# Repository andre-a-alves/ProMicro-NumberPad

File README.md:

# ProMicro-NumberPad

This is a simple learning project that includes the design for a simple numpad PCB that is designed to work with an Arduino-compatible Sparkfun Pro Micro.
The PCB is designed in Autodesk Eagle, and the C code is written for the Arduino IDE.

## PCB

## License
This project is licensed under the [GNU General Purpose License v3.0](LICENSE).

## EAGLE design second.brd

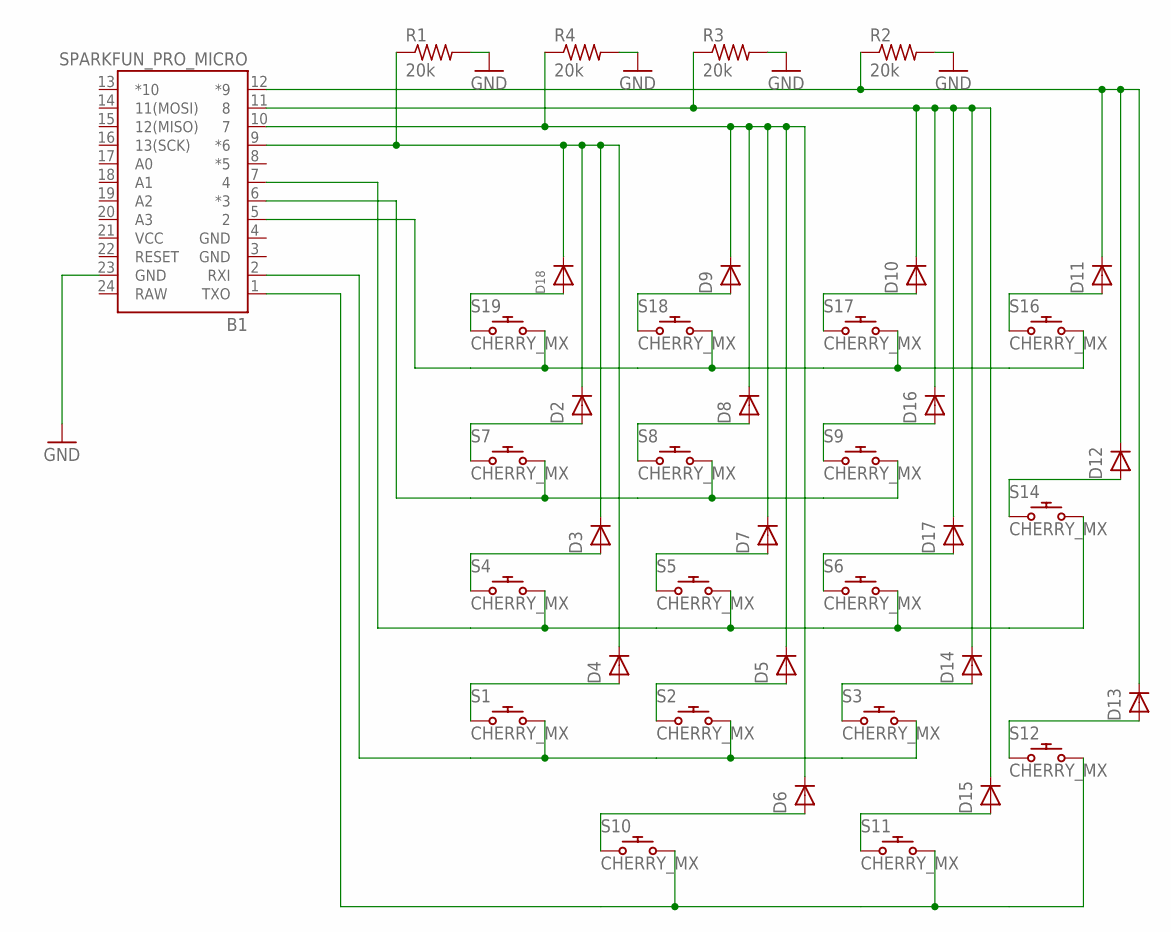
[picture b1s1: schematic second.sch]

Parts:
B1: SPARKFUN_PRO_MICRO
D2, D3, D4, D5, D6, D7, D8, D9, D10, D11, D12, D13, D14, D15, D16, D17, D18: DIODESOD-123; SOD-123
R1, R2, R3, R4: 20k; R0805
S1, S2, S3, S4, S5, S6, S7, S8, S9, S10, S11, S12, S14, S16, S17, S18, S19: CHERRY_MX

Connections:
GND: B1.3 (GND), B1.4 (GND), B1.23 (GND), R1.2, R2.2, R3.2, R4.2
unnamed: D3.A, S4.S1 (1)
unnamed: D2.A, S7.S1 (1)
unnamed: D6.A, S10.S1 (1)
unnamed: D4.A, S1.S1 (1)
unnamed: D7.A, S5.S1 (1)
unnamed: D8.A, S8.S1 (1)
unnamed: D15.A, S11.S1 (1)
unnamed: D16.A, S9.S1 (1)
unnamed: D17.A, S6.S1 (1)
unnamed: D5.A, S2.S1 (1)
unnamed: D14.A, S3.S1 (1)
unnamed: D13.A, S12.S1 (1)
unnamed: D10.A, S17.S1 (1)
unnamed: D12.A, S14.S1 (1)
unnamed: D9.A, S18.S1 (1)
unnamed: B1.9 (*6), D2.C, D3.C, D4.C, D18.C, R1.1
unnamed: D18.A, S19.S1 (1)
unnamed: D11.A, S16.S1 (1)
unnamed: B1.1 (TXO), S10.S2 (2), S11.S2 (2), S12.S2 (2)
unnamed: B1.2 (RXI), S1.S2 (2), S2.S2 (2), S3.S2 (2)
unnamed: B1.7 (4), S4.S2 (2), S5.S2 (2), S6.S2 (2), S14.S2 (2)
unnamed: B1.6 (*3), S7.S2 (2), S8.S2 (2), S9.S2 (2)
unnamed: B1.5 (2), S16.S2 (2), S17.S2 (2), S18.S2 (2), S19.S2 (2)
unnamed: B1.10 (7), D5.C, D6.C, D7.C, D8.C, D9.C, R4.1
unnamed: B1.11 (8), D10.C, D14.C, D15.C, D16.C, D17.C, R3.1
unnamed: B1.12 (*9), D11.C, D12.C, D13.C, R2.1
RAW: B1.24 (RAW)
VCC: B1.21 (VCC)

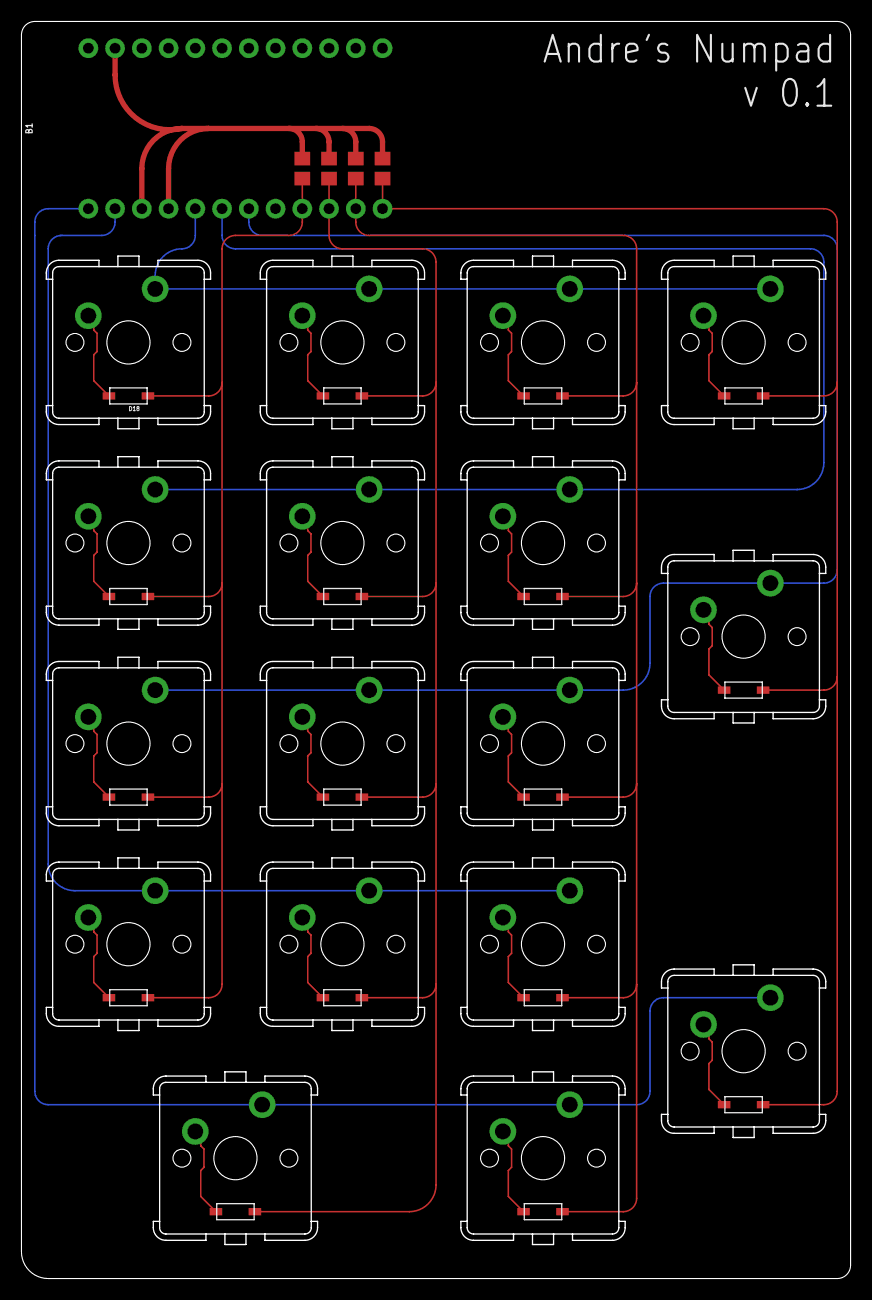
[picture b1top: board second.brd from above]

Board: 2 copper layers, 78.7 x 119.3 mm, 39 parts (0 on the bottom side), 27 nets.

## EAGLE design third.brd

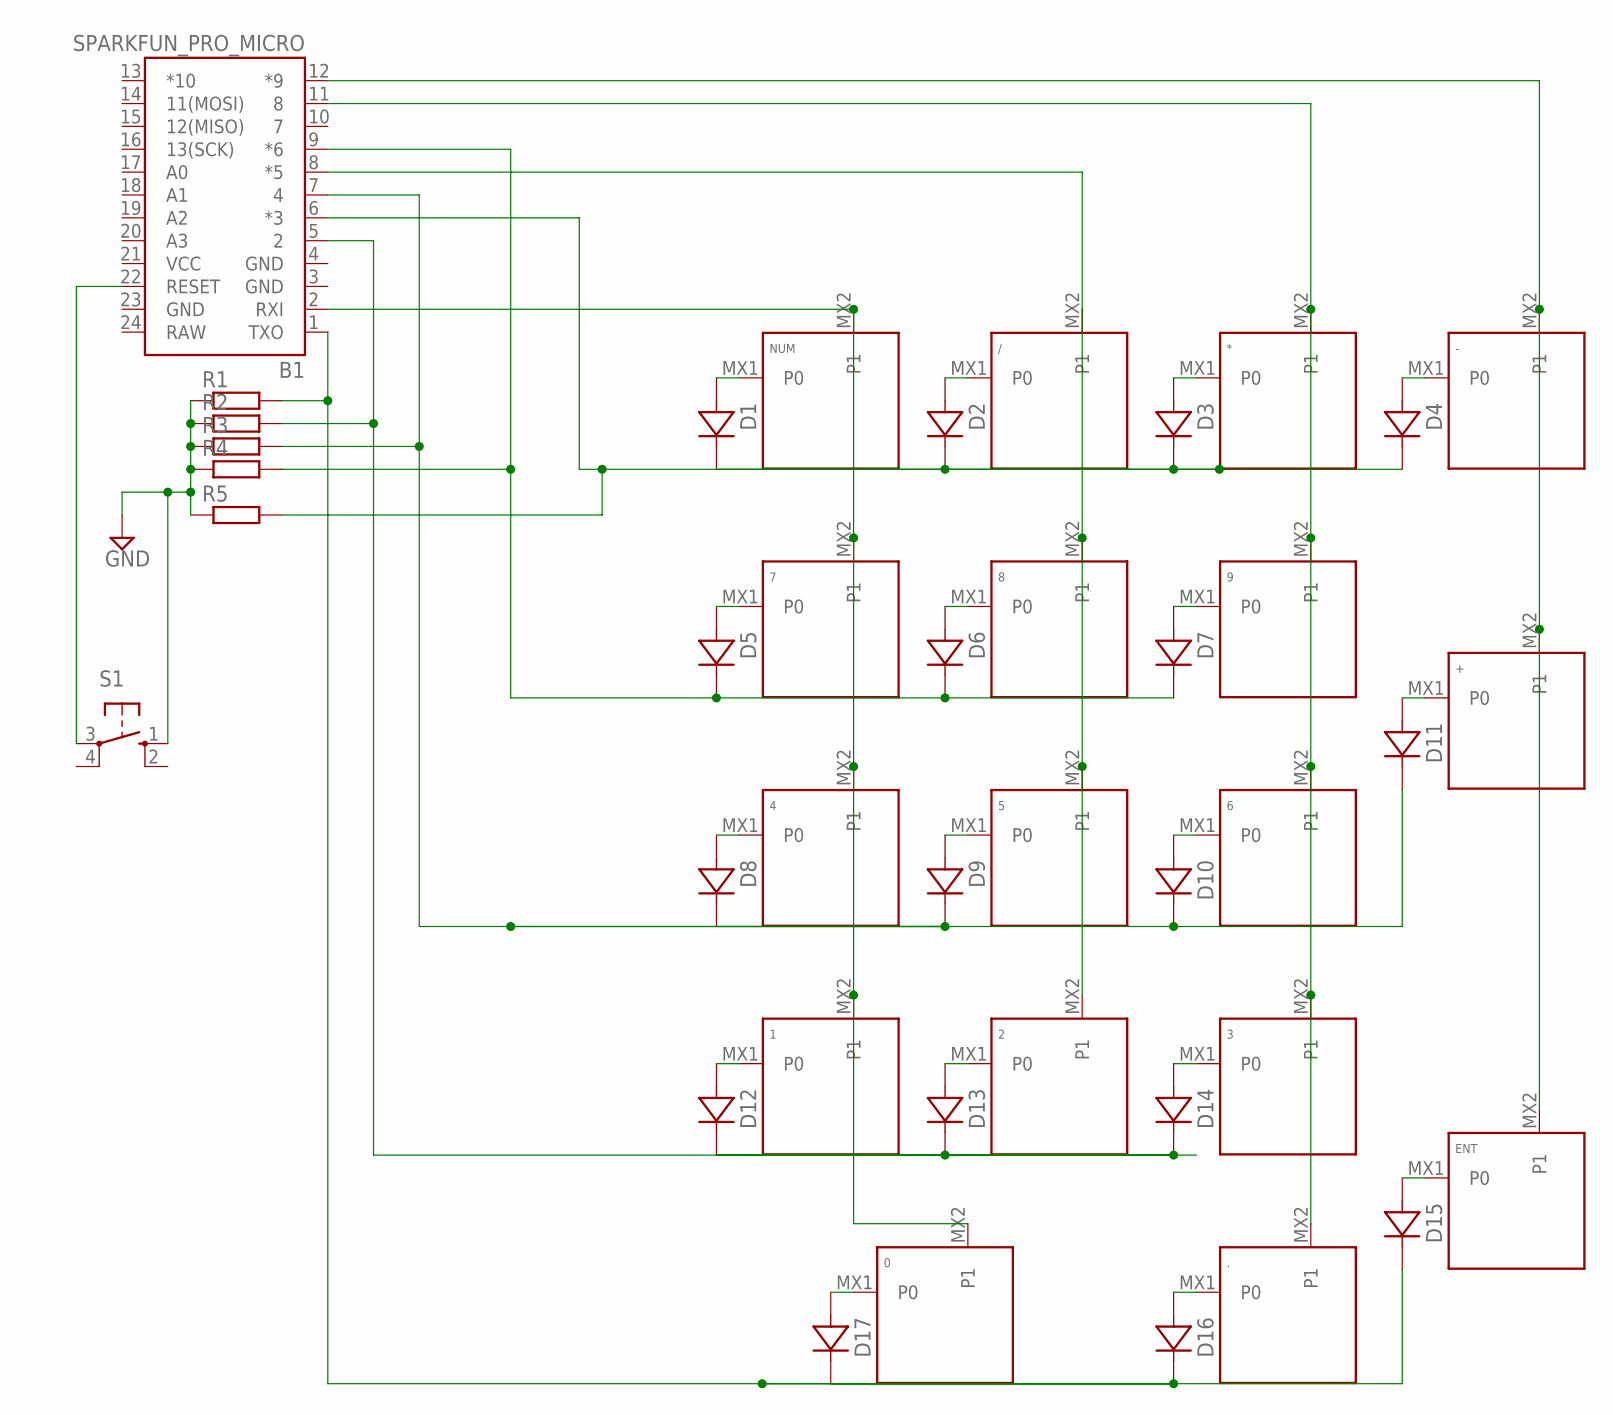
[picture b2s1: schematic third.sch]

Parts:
0: KEYSWITCH-PLAIN-MX-2U-FLIPPED; MX-2U-FLIPPED
1, 2, 3, 4, 5, 6, 7, 8, 9, .: KEYSWITCH-PLAIN-MX-1U; MX-1U
*: KEYSWITCH-PLAIN-MX-1U; MX-1U
+: KEYSWITCH-PLAIN-MX-2U-ROTATED; MX-2U-ROTATED
-: KEYSWITCH-PLAIN-MX-1U; MX-1U
/: KEYSWITCH-PLAIN-MX-1U; MX-1U
B1: SPARKFUN_PRO_MICRO
D1, D2, D3, D4, D5, D6, D7, D8, D9, D10, D11, D12, D13, D14, D15, D16, D17: 1N4148; DIODE_HAND
ENT: KEYSWITCH-PLAIN-MX-2U-ROTATED; MX-2U-ROTATED
NUM: KEYSWITCH-PLAIN-MX-1U; MX-1U
R1, R2, R3, R4, R5: RESISTOR-THT; THT-RESISTOR
S1: 10-XX; B3F-10XX

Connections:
GND: B1.3 (GND), B1.4 (GND), B1.23 (GND), R1.1, R2.1, R3.1, R4.1, R5.1, S1.1 (S)
unnamed: D1.A1 (A), D1.A2 (A), D1.A3 (A), NUM.MX1 (P0)
unnamed: /.MX1 (P0), D2.A1 (A), D2.A2 (A), D2.A3 (A)
unnamed: *.MX1 (P0), D3.A1 (A), D3.A2 (A), D3.A3 (A)
unnamed: -.MX1 (P0), D4.A1 (A), D4.A2 (A), D4.A3 (A)
unnamed: 7.MX1 (P0), D5.A1 (A), D5.A2 (A), D5.A3 (A)
unnamed: 8.MX1 (P0), D6.A1 (A), D6.A2 (A), D6.A3 (A)
unnamed: 9.MX1 (P0), D7.A1 (A), D7.A2 (A), D7.A3 (A)
unnamed: 4.MX1 (P0), D8.A1 (A), D8.A2 (A), D8.A3 (A)
unnamed: 5.MX1 (P0), D9.A1 (A), D9.A2 (A), D9.A3 (A)
unnamed: 6.MX1 (P0), D10.A1 (A), D10.A2 (A), D10.A3 (A)
unnamed: +.MX1 (P0), D11.A1 (A), D11.A2 (A), D11.A3 (A)
unnamed: 1.MX1 (P0), D12.A1 (A), D12.A2 (A), D12.A3 (A)
unnamed: 2.MX1 (P0), D13.A1 (A), D13.A2 (A), D13.A3 (A)
unnamed: 3.MX1 (P0), D14.A1 (A), D14.A2 (A), D14.A3 (A)
unnamed: D15.A1 (A), D15.A2 (A), D15.A3 (A), ENT.MX1 (P0)
unnamed: ..MX1 (P0), D16.A1 (A), D16.A2 (A), D16.A3 (A)
unnamed: 0.MX1 (P0), D17.A1 (A), D17.A2 (A), D17.A3 (A)
unnamed: 0.MX2 (P1), 1.MX2 (P1), 4.MX2 (P1), 7.MX2 (P1), B1.2 (RXI), NUM.MX2 (P1)
unnamed: 2.MX2 (P1), 5.MX2 (P1), 8.MX2 (P1), /.MX2 (P1), B1.8 (*5)
unnamed: 3.MX2 (P1), 6.MX2 (P1), 9.MX2 (P1), *.MX2 (P1), ..MX2 (P1), B1.11 (8)
unnamed: B1.6 (*3), D1.C1 (C), D1.C2 (C), D1.C3 (C), D2.C1 (C), D2.C2 (C), D2.C3 (C), D3.C1 (C), D3.C2 (C), D3.C3 (C), D4.C1 (C), D4.C2 (C), D4.C3 (C), R5.2
unnamed: B1.9 (*6), D5.C1 (C), D5.C2 (C), D5.C3 (C), D6.C1 (C), D6.C2 (C), D6.C3 (C), D7.C1 (C), D7.C2 (C), D7.C3 (C), R4.2
unnamed: B1.7 (4), D8.C1 (C), D8.C2 (C), D8.C3 (C), D9.C1 (C), D9.C2 (C), D9.C3 (C), D10.C1 (C), D10.C2 (C), D10.C3 (C), D11.C1 (C), D11.C2 (C), D11.C3 (C), R3.2
unnamed: B1.5 (2), D12.C1 (C), D12.C2 (C), D12.C3 (C), D13.C1 (C), D13.C2 (C), D13.C3 (C), D14.C1 (C), D14.C2 (C), D14.C3 (C), R2.2
unnamed: B1.1 (TXO), D15.C1 (C), D15.C2 (C), D15.C3 (C), D16.C1 (C), D16.C2 (C), D16.C3 (C), D17.C1 (C), D17.C2 (C), D17.C3 (C), R1.2
unnamed: B1.22 (RESET), S1.3
unnamed: +.MX2 (P1), -.MX2 (P1), B1.12 (*9), ENT.MX2 (P1)
RAW: B1.24 (RAW)
VCC: B1.21 (VCC)

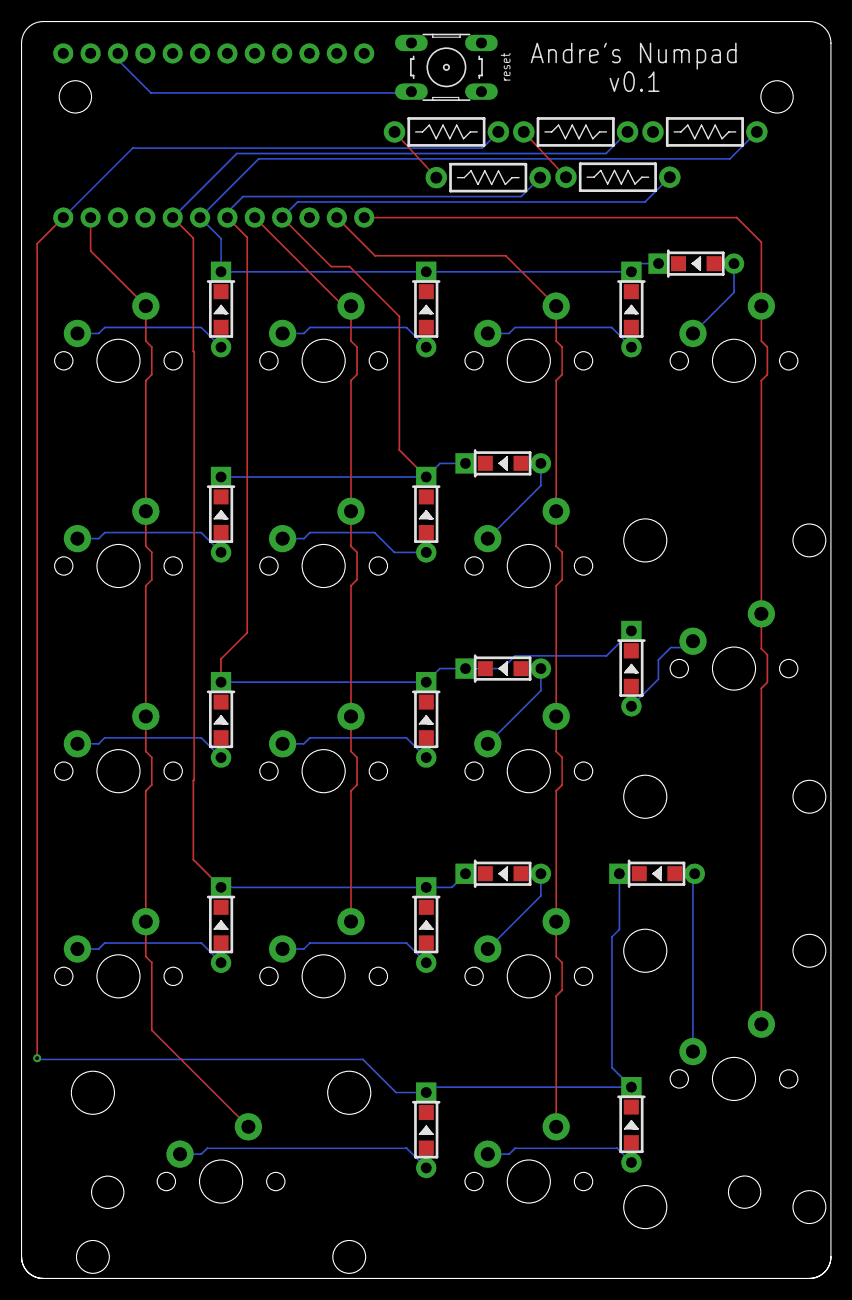
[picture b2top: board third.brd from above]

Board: 2 copper layers, 75.2 x 116.7 mm, 41 parts (0 on the bottom side), 28 nets.

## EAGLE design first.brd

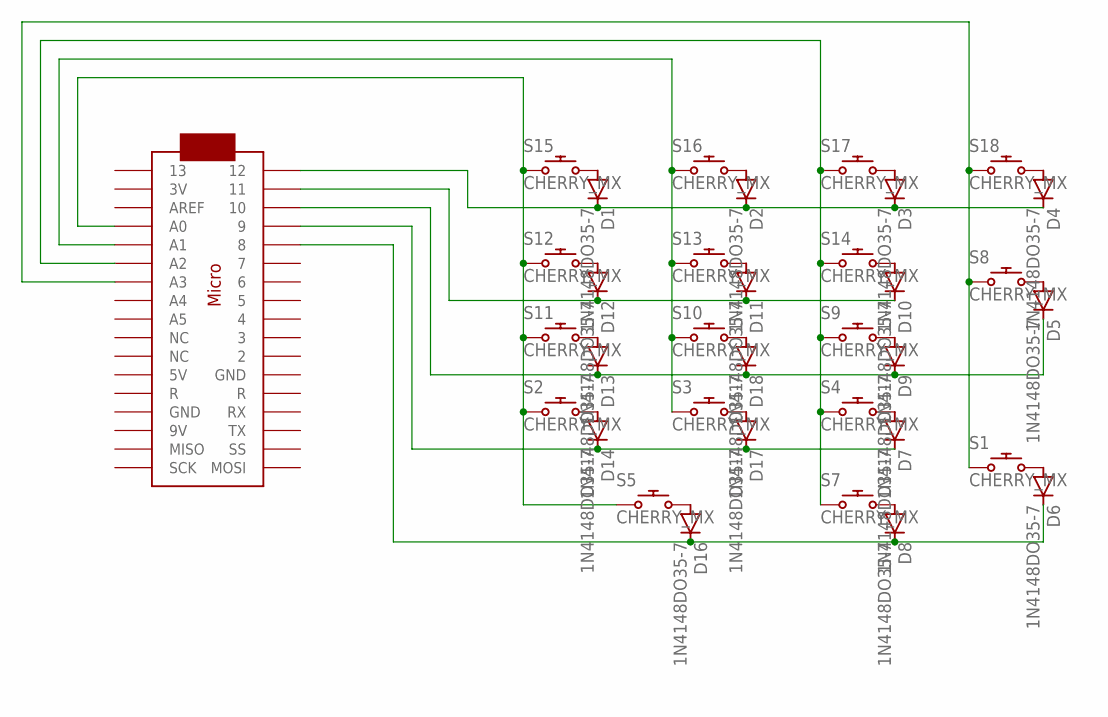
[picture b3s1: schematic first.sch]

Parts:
D1, D2, D3, D4, D5, D6, D7, D8, D9, D10, D11, D12, D13, D14, D16, D17, D18: 1N4148DO35-7; DO35-7
S1, S2, S3, S4, S5, S7, S8, S9, S10, S11, S12, S13, S14, S15, S16, S17, S18: CHERRY_MX
U$1: ARDUINOMICRO

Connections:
unnamed: S2.S1 (1), S5.S1 (1), S11.S1 (1), S12.S1 (1), S15.S1 (1), U$1.P$31 (A0)
unnamed: S3.S1 (1), S10.S1 (1), S13.S1 (1), S16.S1 (1), U$1.P$30 (A1)
unnamed: S4.S1 (1), S7.S1 (1), S9.S1 (1), S14.S1 (1), S17.S1 (1), U$1.P$29 (A2)
unnamed: S1.S1 (1), S8.S1 (1), S18.S1 (1), U$1.P$28 (A3)
unnamed: D1.C, D2.C, D3.C, D4.C, U$1.P$1 (12)
unnamed: D10.C, D11.C, D12.C, U$1.P$2 (11)
unnamed: D5.C, D9.C, D13.C, D18.C, U$1.P$3 (10)
unnamed: D7.C, D14.C, D17.C, U$1.P$4 (9)
unnamed: D6.C, D8.C, D16.C, U$1.P$5 (8)
unnamed: D1.A, S15.S2 (2)
unnamed: D2.A, S16.S2 (2)
unnamed: D3.A, S17.S2 (2)
unnamed: D4.A, S18.S2 (2)
unnamed: D5.A, S8.S2 (2)
unnamed: D6.A, S1.S2 (2)
unnamed: D7.A, S4.S2 (2)
unnamed: D8.A, S7.S2 (2)
unnamed: D9.A, S9.S2 (2)
unnamed: D10.A, S14.S2 (2)
unnamed: D11.A, S13.S2 (2)
unnamed: D12.A, S12.S2 (2)
unnamed: D13.A, S11.S2 (2)
unnamed: D14.A, S2.S2 (2)
unnamed: D16.A, S5.S2 (2)
unnamed: D17.A, S3.S2 (2)
unnamed: D18.A, S10.S2 (2)

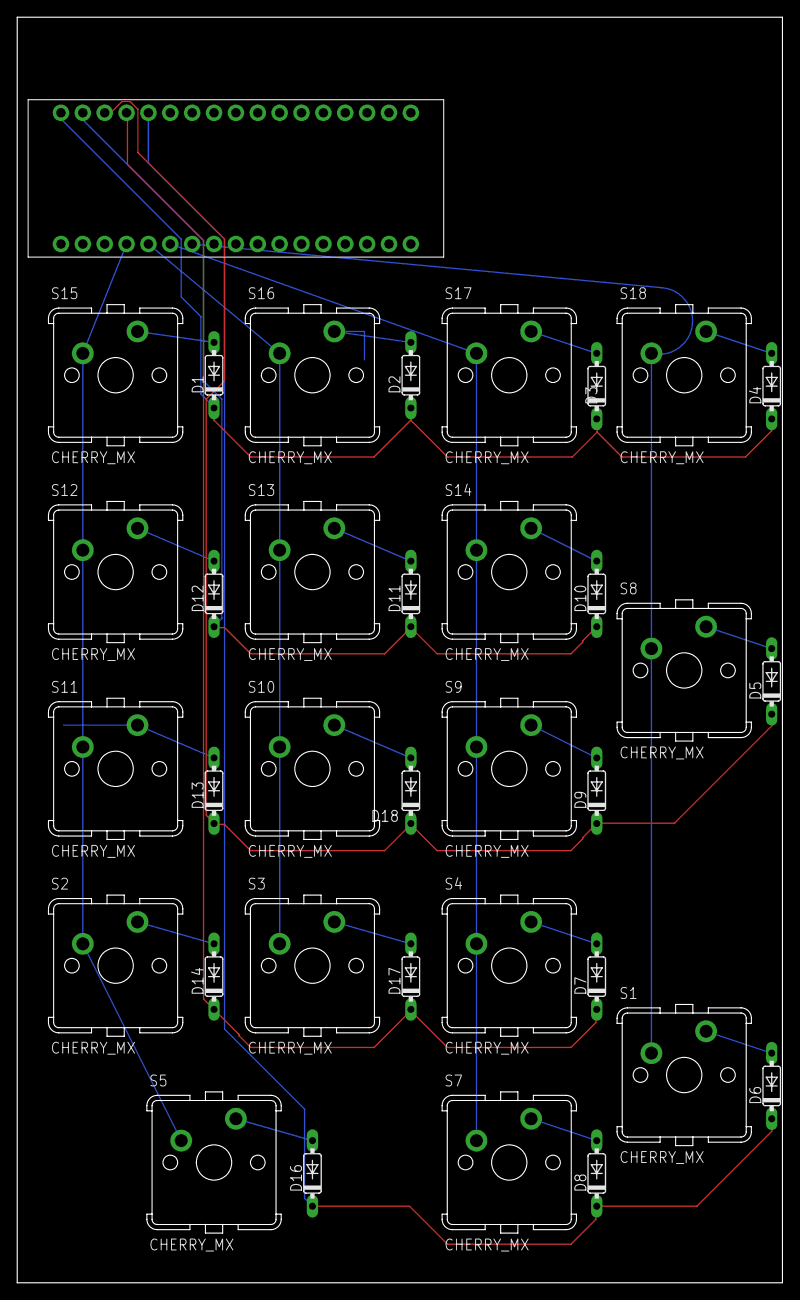
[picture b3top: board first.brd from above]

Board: 2 copper layers, 88.8 x 146.9 mm, 35 parts (0 on the bottom side), 26 nets.

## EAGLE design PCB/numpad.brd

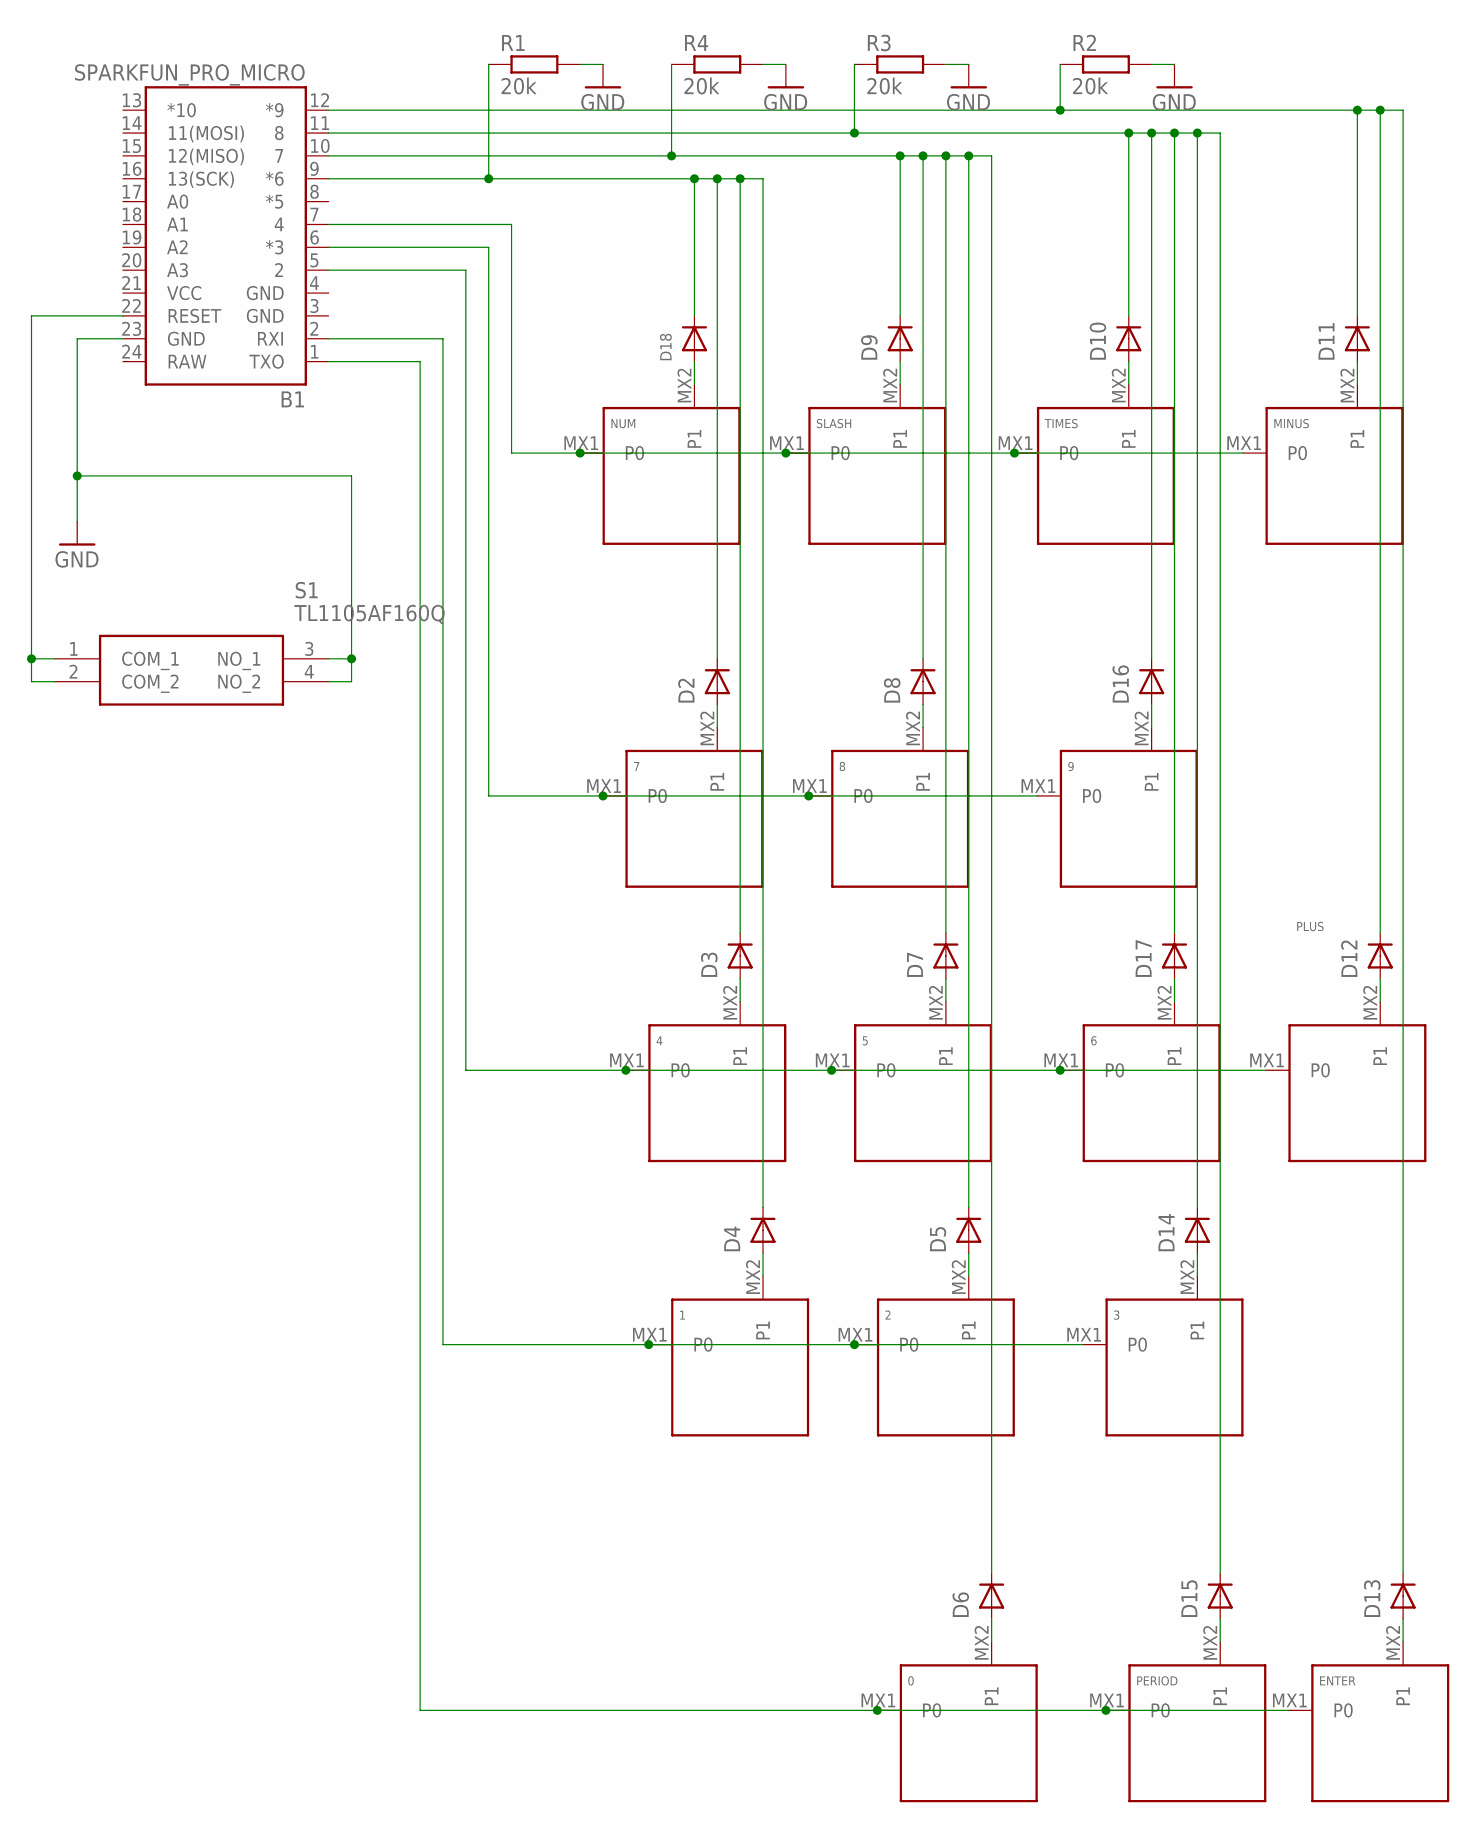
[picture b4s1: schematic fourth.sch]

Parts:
0: KEYSWITCH-PLAIN-MX-2U-FLIPPED; MX-2U-FLIPPED
1, 2, 3, 4, 5, 6, 7, 8, 9: KEYSWITCH-PLAIN-MX-1U; MX-1U
B1: SPARKFUN_PRO_MICRO
D2, D3, D4, D5, D6, D7, D8, D9, D10, D11, D12, D13, D14, D15, D16, D17, D18: DIODEDO-1N4148; DO-1N4148
ENTER: KEYSWITCH-PLAIN-MX-2U-ROTATED; MX-2U-ROTATED
MINUS: KEYSWITCH-PLAIN-MX-1U; MX-1U
NUM: KEYSWITCH-PLAIN-MX-1U; MX-1U
PERIOD: KEYSWITCH-PLAIN-MX-1U; MX-1U
PLUS: KEYSWITCH-PLAIN-MX-2U-ROTATED; MX-2U-ROTATED
R1, R2, R3, R4: 20k; THT-RESISTOR
S1: TL1105AF160Q
SLASH: KEYSWITCH-PLAIN-MX-1U; MX-1U
TIMES: KEYSWITCH-PLAIN-MX-1U; MX-1U

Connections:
GND: B1.3 (GND), B1.4 (GND), B1.23 (GND), R1.2, R2.2, R3.2, R4.2, S1.3 (NO_1), S1.4 (NO_2)
unnamed: 7.MX2 (P1), D2.A
unnamed: 4.MX2 (P1), D3.A
unnamed: 1.MX2 (P1), D4.A
unnamed: 2.MX2 (P1), D5.A
unnamed: 0.MX2 (P1), D6.A
unnamed: 5.MX2 (P1), D7.A
unnamed: 8.MX2 (P1), D8.A
unnamed: D9.A, SLASH.MX2 (P1)
unnamed: D10.A, TIMES.MX2 (P1)
unnamed: D11.A, MINUS.MX2 (P1)
unnamed: D12.A, PLUS.MX2 (P1)
unnamed: D13.A, ENTER.MX2 (P1)
unnamed: 3.MX2 (P1), D14.A
unnamed: D15.A, PERIOD.MX2 (P1)
unnamed: 9.MX2 (P1), D16.A
unnamed: B1.9 (*6), D2.C, D3.C, D4.C, D18.C, R1.1
unnamed: 6.MX2 (P1), D17.A
unnamed: D18.A, NUM.MX2 (P1)
unnamed: 0.MX1 (P0), B1.1 (TXO), ENTER.MX1 (P0), PERIOD.MX1 (P0)
unnamed: 1.MX1 (P0), 2.MX1 (P0), 3.MX1 (P0), B1.2 (RXI)
unnamed: 4.MX1 (P0), 5.MX1 (P0), 6.MX1 (P0), B1.5 (2), PLUS.MX1 (P0)
unnamed: 7.MX1 (P0), 8.MX1 (P0), 9.MX1 (P0), B1.6 (*3)
unnamed: B1.7 (4), MINUS.MX1 (P0), NUM.MX1 (P0), SLASH.MX1 (P0), TIMES.MX1 (P0)
unnamed: B1.22 (RESET), S1.1 (COM_1), S1.2 (COM_2)
unnamed: B1.10 (7), D5.C, D6.C, D7.C, D8.C, D9.C, R4.1
unnamed: B1.11 (8), D10.C, D14.C, D15.C, D16.C, D17.C, R3.1
unnamed: B1.12 (*9), D11.C, D12.C, D13.C, R2.1
RAW: B1.24 (RAW)
VCC: B1.21 (VCC)

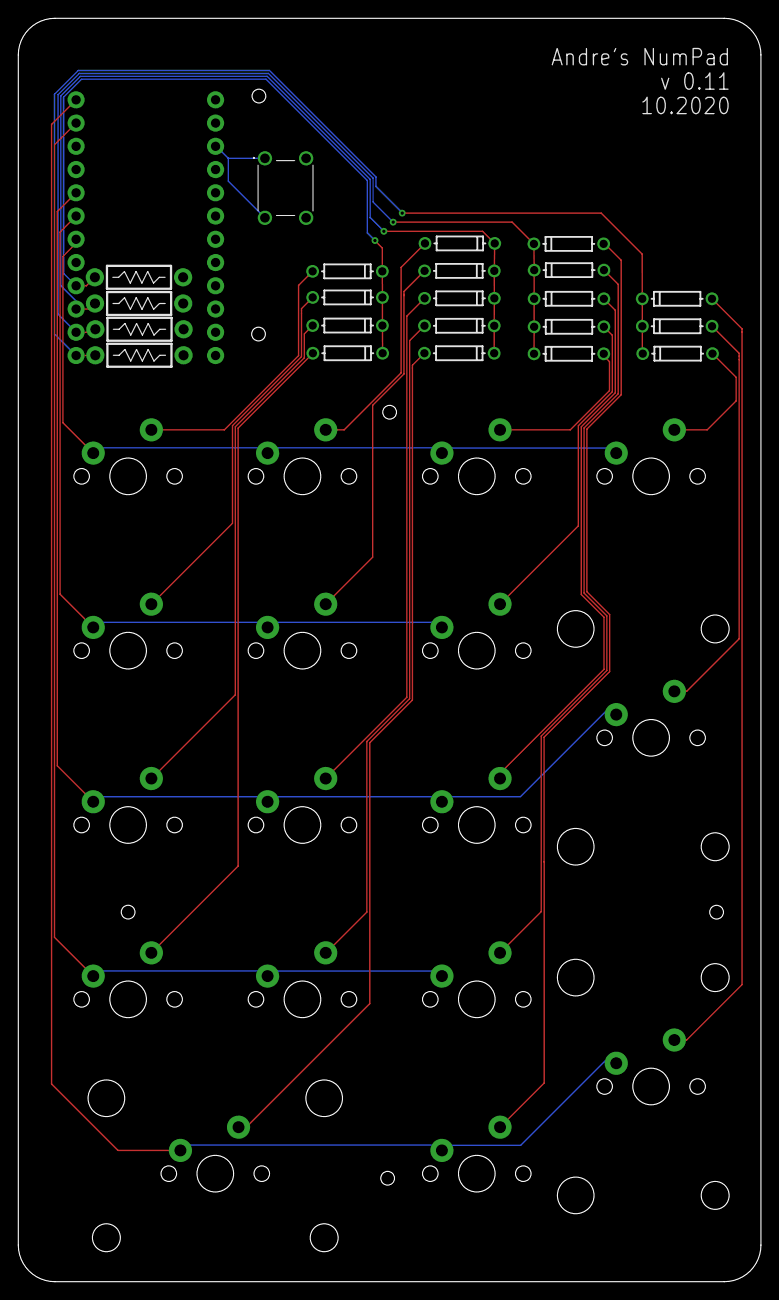
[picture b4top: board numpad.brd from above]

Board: 2 copper layers, 81.2 x 138.1 mm, 40 parts (0 on the bottom side), 28 nets.

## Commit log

2022-02-06 Readme updated and files cleaned up for presentation

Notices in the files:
parts and their libraries:
SparkFun-Boards: Licensing: Creative Commons ShareAlike 4.0 International - https://creativecommons.org/licenses/by-sa/4.0
